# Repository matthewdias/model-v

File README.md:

# model-v

Info here
https://trashman.wiki/en/community/pcbs/model-v

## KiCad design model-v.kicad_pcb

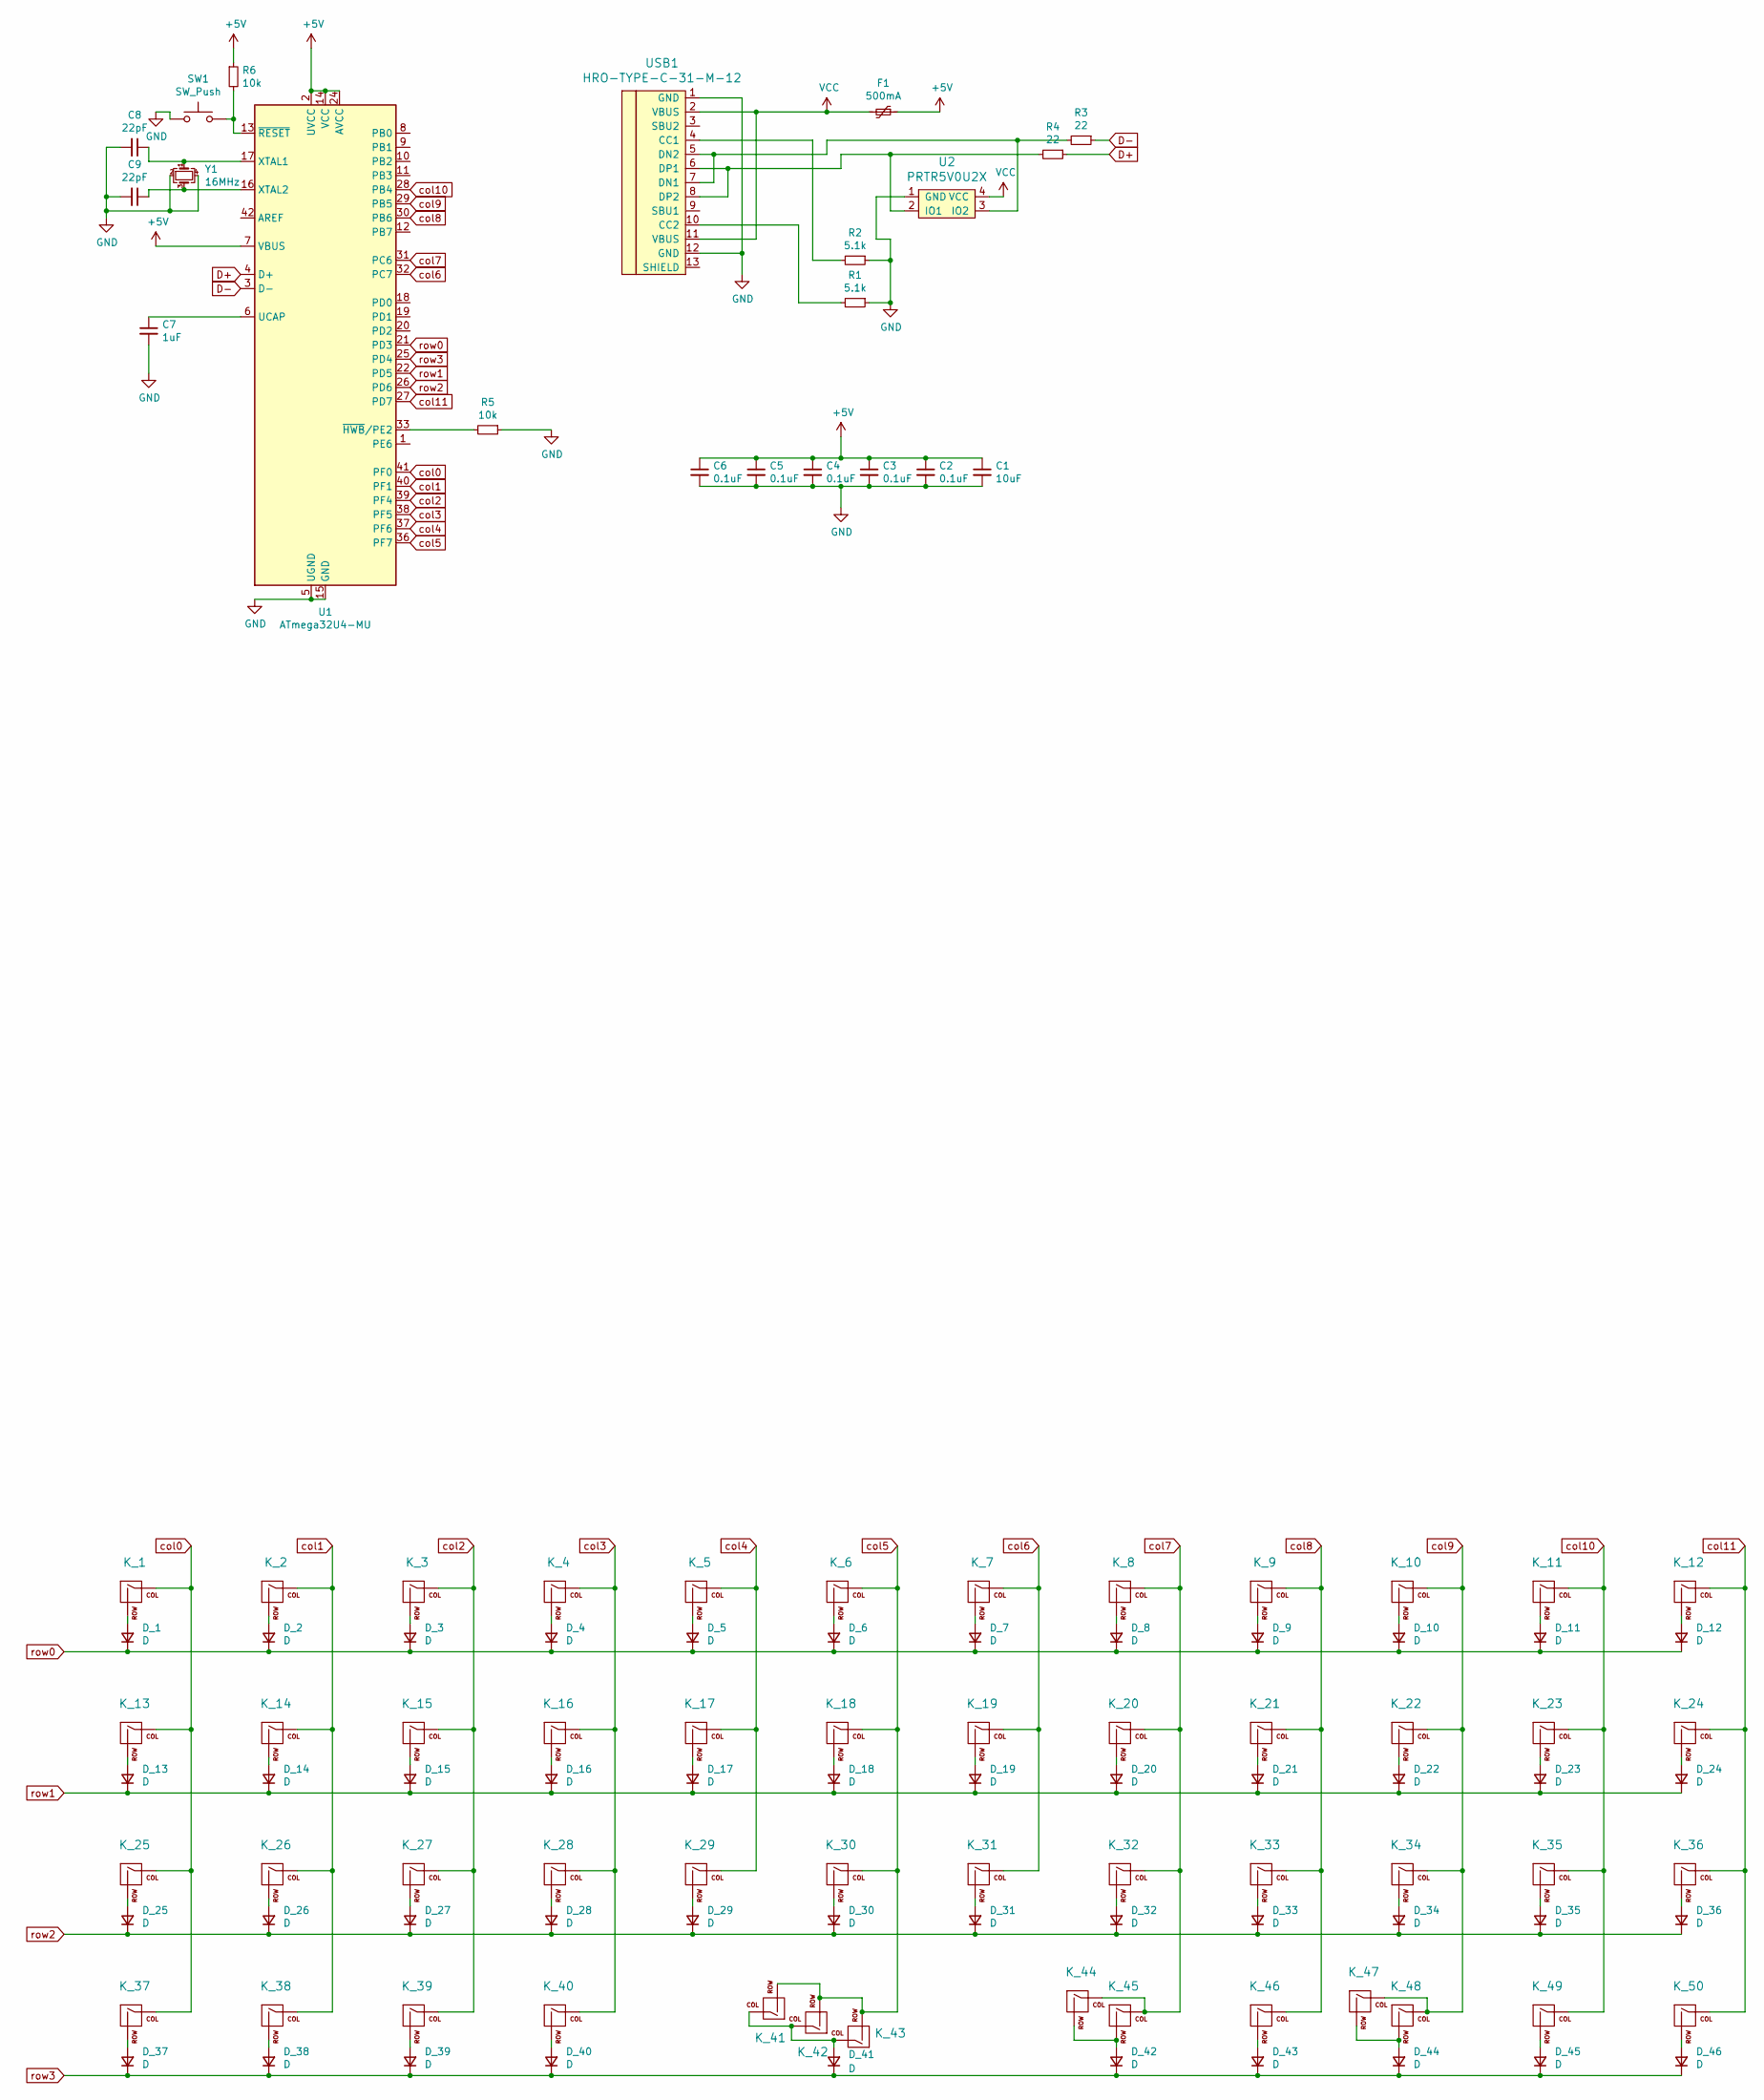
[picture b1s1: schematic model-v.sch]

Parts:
C1: 10uF; C_0603_1608Metric
C2, C3, C4, C5, C6: 0.1uF; C_0603_1608Metric
C7: 1uF; C_0603_1608Metric
C8, C9: 22pF; C_0603_1608Metric
D_1, D_2, D_3, D_4, D_5, D_6, D_7, D_8, D_9, D_10, D_11, D_12, D_13, D_14, D_15, D_16, D_17, D_18, D_19, D_20, D_21, D_22, D_23, D_24, D_25, D_26, D_27, D_28, D_29, D_30, D_31, D_32, D_33, D_34, D_35, D_36, D_37, D_38, D_39, D_40, D_41, D_42, D_43, D_44, D_45, D_46: D; D_SOD-123
F1: 500mA; Fuse_1206_3216Metric
K_1, K_2, K_3, K_4, K_5, K_6, K_7, K_8, K_9, K_10, K_11, K_14, K_15, K_16, K_17, K_18, K_19, K_20, K_21, K_22, K_23, K_26, K_27, K_28, K_29, K_30, K_31, K_32, K_33, K_34, K_35, K_36, K_38, K_40, K_46, K_48, K_49, K_50: KEYSW; MXOnly-1U-NoLED
K_12, K_25: KEYSW; MXOnly-1.75U-NoLED
K_13, K_37, K_39, K_47: KEYSW; MXOnly-1.25U-NoLED
K_24: KEYSW; MXOnly-1.5U-NoLED
K_41, K_45: KEYSW; MXOnly-3U-ReversedStabilizers-NoLED
K_42: KEYSW; MXOnly-2.25U-ReversedStabilizers-NoLED
K_43: KEYSW; MXOnly-6.25U-ReversedStabilizers-NoLED
K_44: KEYSW; MXOnly-2U-ReversedStabilizers-NoLED
R1, R2: 5.1k; R_0603_1608Metric
R3, R4: 22; R_0603_1608Metric
R5, R6: 10k; R_0603_1608Metric
SW1: SW_Push; SW_Push_SPST_NO_Alps_SKRK
U1: ATmega32U4-MU; QFN-44-1EP_7x7mm_P0.5mm_EP5.2x5.2mm
U2: PRTR5V0U2X; SOT143B
USB1: HRO-TYPE-C-31-M-12; HRO-TYPE-C-31-M-12-Assembly
Y1: 16MHz; Crystal_SMD_3225-4Pin_3.2x2.5mm

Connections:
+5V: C1.1, C2.1, C3.1, C4.1, C5.1, C6.1, F1.1, R6.1, U1.2 (UVCC), U1.7 (VBUS), U1.14 (VCC), U1.24 (AVCC), U1.34 (VCC), U1.44 (AVCC)
D+: R4.1, U1.4 (D+)
D-: R3.1, U1.3 (D-)
GND: C1.2, C2.2, C3.2, C4.2, C5.2, C6.2, C7.2, C8.2, C9.2, R1.1, R2.1, R5.1, SW1.1, U1.5 (UGND), U1.15 (GND), U1.23 (GND), U1.35 (GND), U1.43 (GND), U1.45 (GND), U2.1 (GND), USB1.1 (GND), USB1.12 (GND), Y1.2, Y1.4
unnamed: C7.1, U1.6 (UCAP)
unnamed: C8.1, U1.17 (XTAL1), Y1.1
unnamed: C9.1, U1.16 (XTAL2), Y1.3
unnamed: D_1.2 (A), K_1.2 (ROW)
unnamed: D_2.2 (A), K_2.2 (ROW)
unnamed: D_3.2 (A), K_3.2 (ROW)
unnamed: D_4.2 (A), K_4.2 (ROW)
unnamed: D_5.2 (A), K_5.2 (ROW)
unnamed: D_6.2 (A), K_6.2 (ROW)
unnamed: D_7.2 (A), K_7.2 (ROW)
unnamed: D_8.2 (A), K_8.2 (ROW)
unnamed: D_9.2 (A), K_9.2 (ROW)
unnamed: D_10.2 (A), K_10.2 (ROW)
unnamed: D_11.2 (A), K_11.2 (ROW)
unnamed: D_12.2 (A), K_12.2 (ROW)
unnamed: D_13.2 (A), K_13.2 (ROW)
unnamed: D_14.2 (A), K_14.2 (ROW)
unnamed: D_15.2 (A), K_15.2 (ROW)
unnamed: D_16.2 (A), K_16.2 (ROW)
unnamed: D_17.2 (A), K_17.2 (ROW)
unnamed: D_18.2 (A), K_18.2 (ROW)
unnamed: D_19.2 (A), K_19.2 (ROW)
unnamed: D_20.2 (A), K_20.2 (ROW)
unnamed: D_21.2 (A), K_21.2 (ROW)
unnamed: D_22.2 (A), K_22.2 (ROW)
unnamed: D_23.2 (A), K_23.2 (ROW)
unnamed: D_24.2 (A), K_24.2 (ROW)
unnamed: D_25.2 (A), K_25.2 (ROW)
unnamed: D_26.2 (A), K_26.2 (ROW)
unnamed: D_27.2 (A), K_27.2 (ROW)
unnamed: D_28.2 (A), K_28.2 (ROW)
unnamed: D_29.2 (A), K_29.2 (ROW)
unnamed: D_30.2 (A), K_30.2 (ROW)
unnamed: D_31.2 (A), K_31.2 (ROW)
unnamed: D_32.2 (A), K_32.2 (ROW)
unnamed: D_33.2 (A), K_33.2 (ROW)
unnamed: D_34.2 (A), K_34.2 (ROW)
unnamed: D_35.2 (A), K_35.2 (ROW)
unnamed: D_36.2 (A), K_36.2 (ROW)
unnamed: D_37.2 (A), K_37.2 (ROW)
unnamed: D_38.2 (A), K_38.2 (ROW)
unnamed: D_39.2 (A), K_39.2 (ROW)
unnamed: D_40.2 (A), K_40.2 (ROW)
unnamed: D_41.2 (A), K_41.1 (COL), K_42.1 (COL), K_43.1 (COL)
unnamed: D_42.2 (A), K_44.2 (ROW), K_45.2 (ROW)
unnamed: D_43.2 (A), K_46.2 (ROW)
unnamed: D_44.2 (A), K_47.2 (ROW), K_48.2 (ROW)
unnamed: D_45.2 (A), K_49.2 (ROW)
unnamed: D_46.2 (A), K_50.2 (ROW)
unnamed: R1.2, USB1.10 (CC2)
unnamed: R2.2, USB1.4 (CC1)
unnamed: R3.2, U2.3 (IO2), USB1.5 (DN2), USB1.7 (DN1)
unnamed: R4.2, U2.2 (IO1), USB1.6 (DP1), USB1.8 (DP2)
unnamed: R5.2, U1.33 (~HWB~/PE2)
unnamed: R6.2, SW1.2, U1.13 (~RESET)
VCC: F1.2, U2.4 (VCC), USB1.2 (VBUS), USB1.11 (VBUS)
col0: K_1.1 (COL), K_13.1 (COL), K_25.1 (COL), K_37.1 (COL), U1.41 (PF0)
col1: K_2.1 (COL), K_14.1 (COL), K_26.1 (COL), K_38.1 (COL), U1.40 (PF1)
col2: K_3.1 (COL), K_15.1 (COL), K_27.1 (COL), K_39.1 (COL), U1.39 (PF4)
col3: K_4.1 (COL), K_16.1 (COL), K_28.1 (COL), K_40.1 (COL), U1.38 (PF5)
col4: K_5.1 (COL), K_17.1 (COL), K_29.1 (COL), U1.37 (PF6)
col5: K_6.1 (COL), K_18.1 (COL), K_30.1 (COL), K_41.2 (ROW), K_42.2 (ROW), K_43.2 (ROW), U1.36 (PF7)
col6: K_7.1 (COL), K_19.1 (COL), K_31.1 (COL), U1.32 (PC7)
col7: K_8.1 (COL), K_20.1 (COL), K_32.1 (COL), K_44.1 (COL), K_45.1 (COL), U1.31 (PC6)
col8: K_9.1 (COL), K_21.1 (COL), K_33.1 (COL), K_46.1 (COL), U1.30 (PB6)
col9: K_10.1 (COL), K_22.1 (COL), K_34.1 (COL), K_47.1 (COL), K_48.1 (COL), U1.29 (PB5)
col10: K_11.1 (COL), K_23.1 (COL), K_35.1 (COL), K_49.1 (COL), U1.28 (PB4)
col11: K_12.1 (COL), K_24.1 (COL), K_36.1 (COL), K_50.1 (COL), U1.27 (PD7)
row0: D_1.1 (K), D_2.1 (K), D_3.1 (K), D_4.1 (K), D_5.1 (K), D_6.1 (K), D_7.1 (K), D_8.1 (K), D_9.1 (K), D_10.1 (K), D_11.1 (K), D_12.1 (K), U1.21 (PD3)
row1: D_13.1 (K), D_14.1 (K), D_15.1 (K), D_16.1 (K), D_17.1 (K), D_18.1 (K), D_19.1 (K), D_20.1 (K), D_21.1 (K), D_22.1 (K), D_23.1 (K), D_24.1 (K), U1.22 (PD5)
row2: D_25.1 (K), D_26.1 (K), D_27.1 (K), D_28.1 (K), D_29.1 (K), D_30.1 (K), D_31.1 (K), D_32.1 (K), D_33.1 (K), D_34.1 (K), D_35.1 (K), D_36.1 (K), U1.26 (PD6)
row3: D_37.1 (K), D_38.1 (K), D_39.1 (K), D_40.1 (K), D_41.1 (K), D_42.1 (K), D_43.1 (K), D_44.1 (K), D_45.1 (K), D_46.1 (K), U1.25 (PD4)

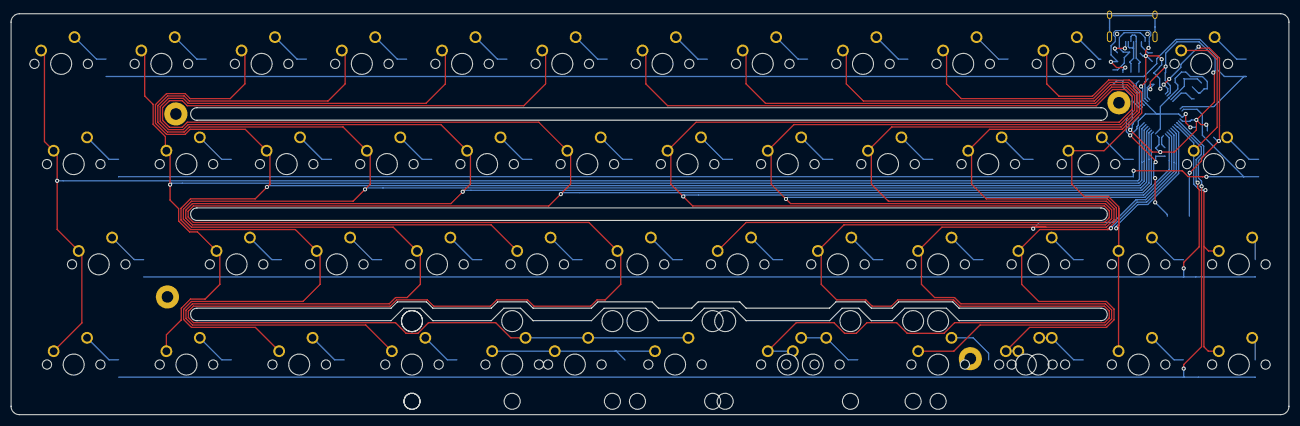
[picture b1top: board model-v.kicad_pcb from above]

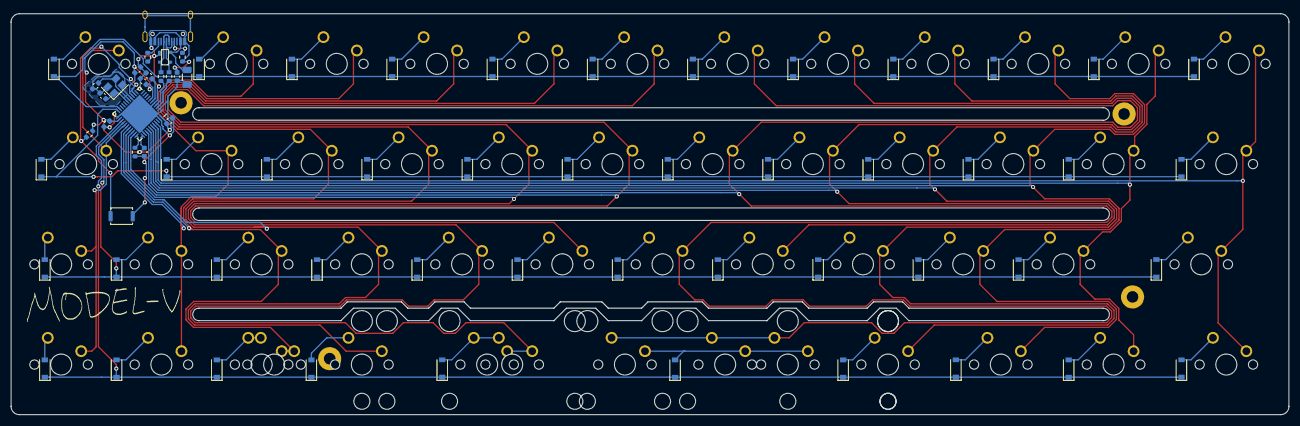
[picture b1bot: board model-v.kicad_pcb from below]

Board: 2 copper layers, 242.9 x 76.2 mm, 121 parts (67 on the bottom side), 76 nets.

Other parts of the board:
H1, H2, H6, H6#2: MountingHole_Pad; MountingHole_2.2mm_M2_Pad

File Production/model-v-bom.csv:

"Designator","Quantity",Value,Footprint,LCSC Part #
"C1, ","1",10uF,0603,C19702
"C2, C3, C4, C5, C6, ","5",0.1uF,0603,C14663
"C7, ","1",1uF,0603,C15849
"C8, C9, ","2",22pF,0603,C1653
"D_1, D_2, D_3, D_4, D_5, D_6, D_7, D_8, D_9, D_10, D_11, D_12, D_13, D_14, D_15, D_16, D_17, D_18, D_19, D_20, D_21, D_22, D_23, D_24, D_25, D_26, D_27, D_28, D_29, D_30, D_31, D_32, D_33, D_34, D_35, D_36, D_37, D_38, D_39, D_40, D_41, D_42, D_43, D_44, D_45, D_46, ","46",D,SOD-123,C64898
"F1, ","1",500mA,1206,C70076
"R1, R2, ","2",5.1k,0603,C23186
"R3, R4, ","2",22,0603,C23345
"R5, R6, ","2",10k,0603,C25804
"SW1, ","1",SW_Push,,C561519
"U1, ","1",ATmega32U4-MU,QFN-44-1EP 7x7mm,C45874
"U2, ","1",PRTR5V0U2X,SOT143B,C12333
"USB1, ","1",HRO-TYPE-C-31-M-12,,C165948
"Y1, ","1",16MHz,3225,C13738

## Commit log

2022-01-17 Update prod files
